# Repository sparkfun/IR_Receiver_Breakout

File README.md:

**NOTE:** *This product has been retired from our catalog. If you are looking for more up-to-date info, please check out some of these resources to see how other users are still hacking and improving on this product.*
* *[SparkFun Forum](https://forum.sparkfun.com/)*
* *[Comments Here on GitHub](https://github.com/sparkfun/IR_Receiver_Breakout/issues)*
* *[IRC Channel](https://www.sparkfun.com/news/263)*

SparkFun IR Receiver Breakout - TSOP85
========================================

[*SparkFun IR Receiver Breakout - TSOP85 (SEN-08554)*](https://www.sparkfun.com/products/8554)

This is a very small infrared receiver based on the TSOP85 receiver from Vishay. This receiver has all the filtering and 38kHz demodulation built into the unit.

Repository Contents
-------------------
* **/Firmware** - Example code 
* **/Hardware** - All Eagle design files (.brd, .sch)

Documentation
--------------
* **[Installing an Arduino Library Guide](https://learn.sparkfun.com/tutorials/installing-an-arduino-library)** - Basic information on how to install an Arduino library.
* **[Library](https://github.com/z3t0/Arduino-IRremote)** - Library library for the IR Control Kit.
* **[IR Communication](https://learn.sparkfun.com/tutorials/ir-communication)** - General tutorial for IR communication.
* **[Hookup Guide](https://learn.sparkfun.com/tutorials/ir-control-kit-hookup-guide)** - Basic hookup guide for the IR Control Kit

Hardware License Information
-------------------

This product is _**open source**_! 

Please review the LICENSE.md file for hardware license information. 
  
Software License Information
-------------------

The example code is derived from the Arduino IRremote library.

Please review Arduino IRremote [LICENSE.md file](https://github.com/z3t0/Arduino-IRremote/blob/master/LICENSE.txt) for license information. 

If you have any questions or concerns on licensing, please contact techsupport@sparkfun.com.

Distributed as-is; no warranty is given.

- Your friends at SparkFun.

_<COLLABORATION CREDIT>_

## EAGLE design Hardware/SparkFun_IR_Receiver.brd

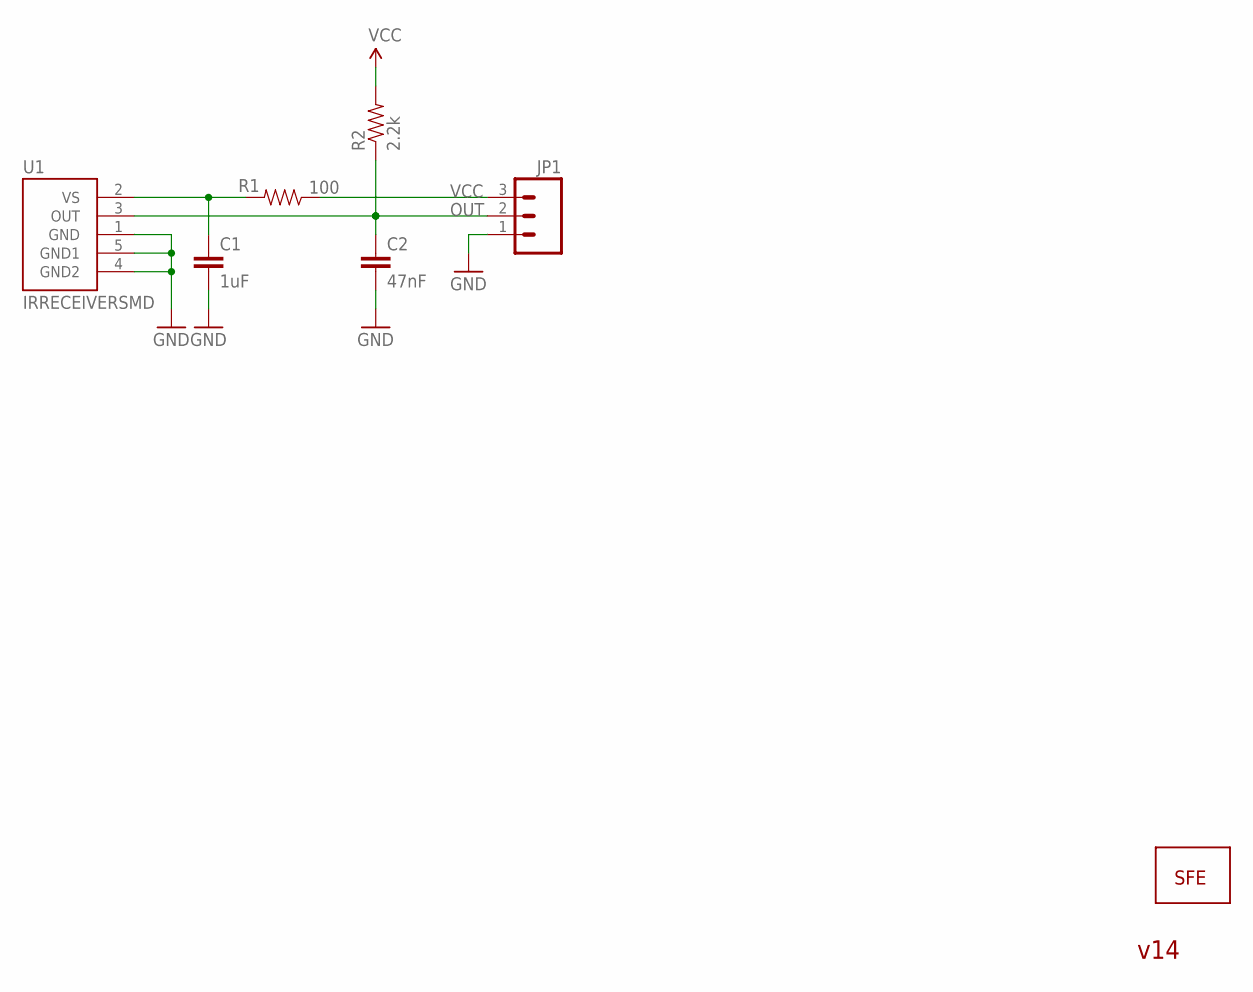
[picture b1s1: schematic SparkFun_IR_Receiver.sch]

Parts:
C1: 1uF; 0603-CAP
C2: 47nF; 0603-CAP
JP1: M03PTH; 1X03
R1: 100; 0603-RES
R2: 2.2k; 0603-RES
U1: IRRECEIVERSMD; TSOP8523
U$1: LOGO-SFESK; SFE-LOGO-FLAME

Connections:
GND: C1.2, C2.2, JP1.1, U1.1 (GND), U1.4 (GND2), U1.5 (GND1)
OUT: C2.1, JP1.2, R2.1, U1.3 (OUT)
VCC: JP1.3, R1.1, R2.2
VS: C1.1, R1.2, U1.2 (VS)

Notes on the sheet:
v14

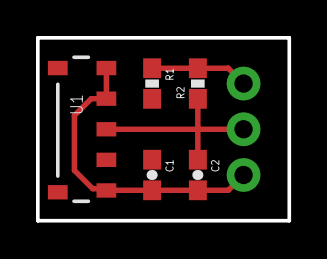
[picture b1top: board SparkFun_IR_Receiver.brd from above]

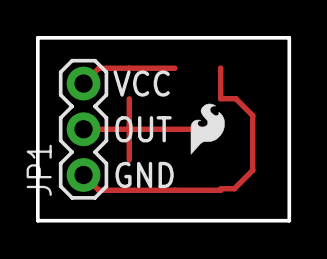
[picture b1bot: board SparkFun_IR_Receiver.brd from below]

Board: 2 copper layers, 14.0 x 10.2 mm, 7 parts (2 on the bottom side), 4 nets.

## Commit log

2015-01-29 Initial hardware files commit
2018-08-11 Rename Remote_Example/Remote_Example.ino to Firmware/Remote_Example/Remote_Example.ino
